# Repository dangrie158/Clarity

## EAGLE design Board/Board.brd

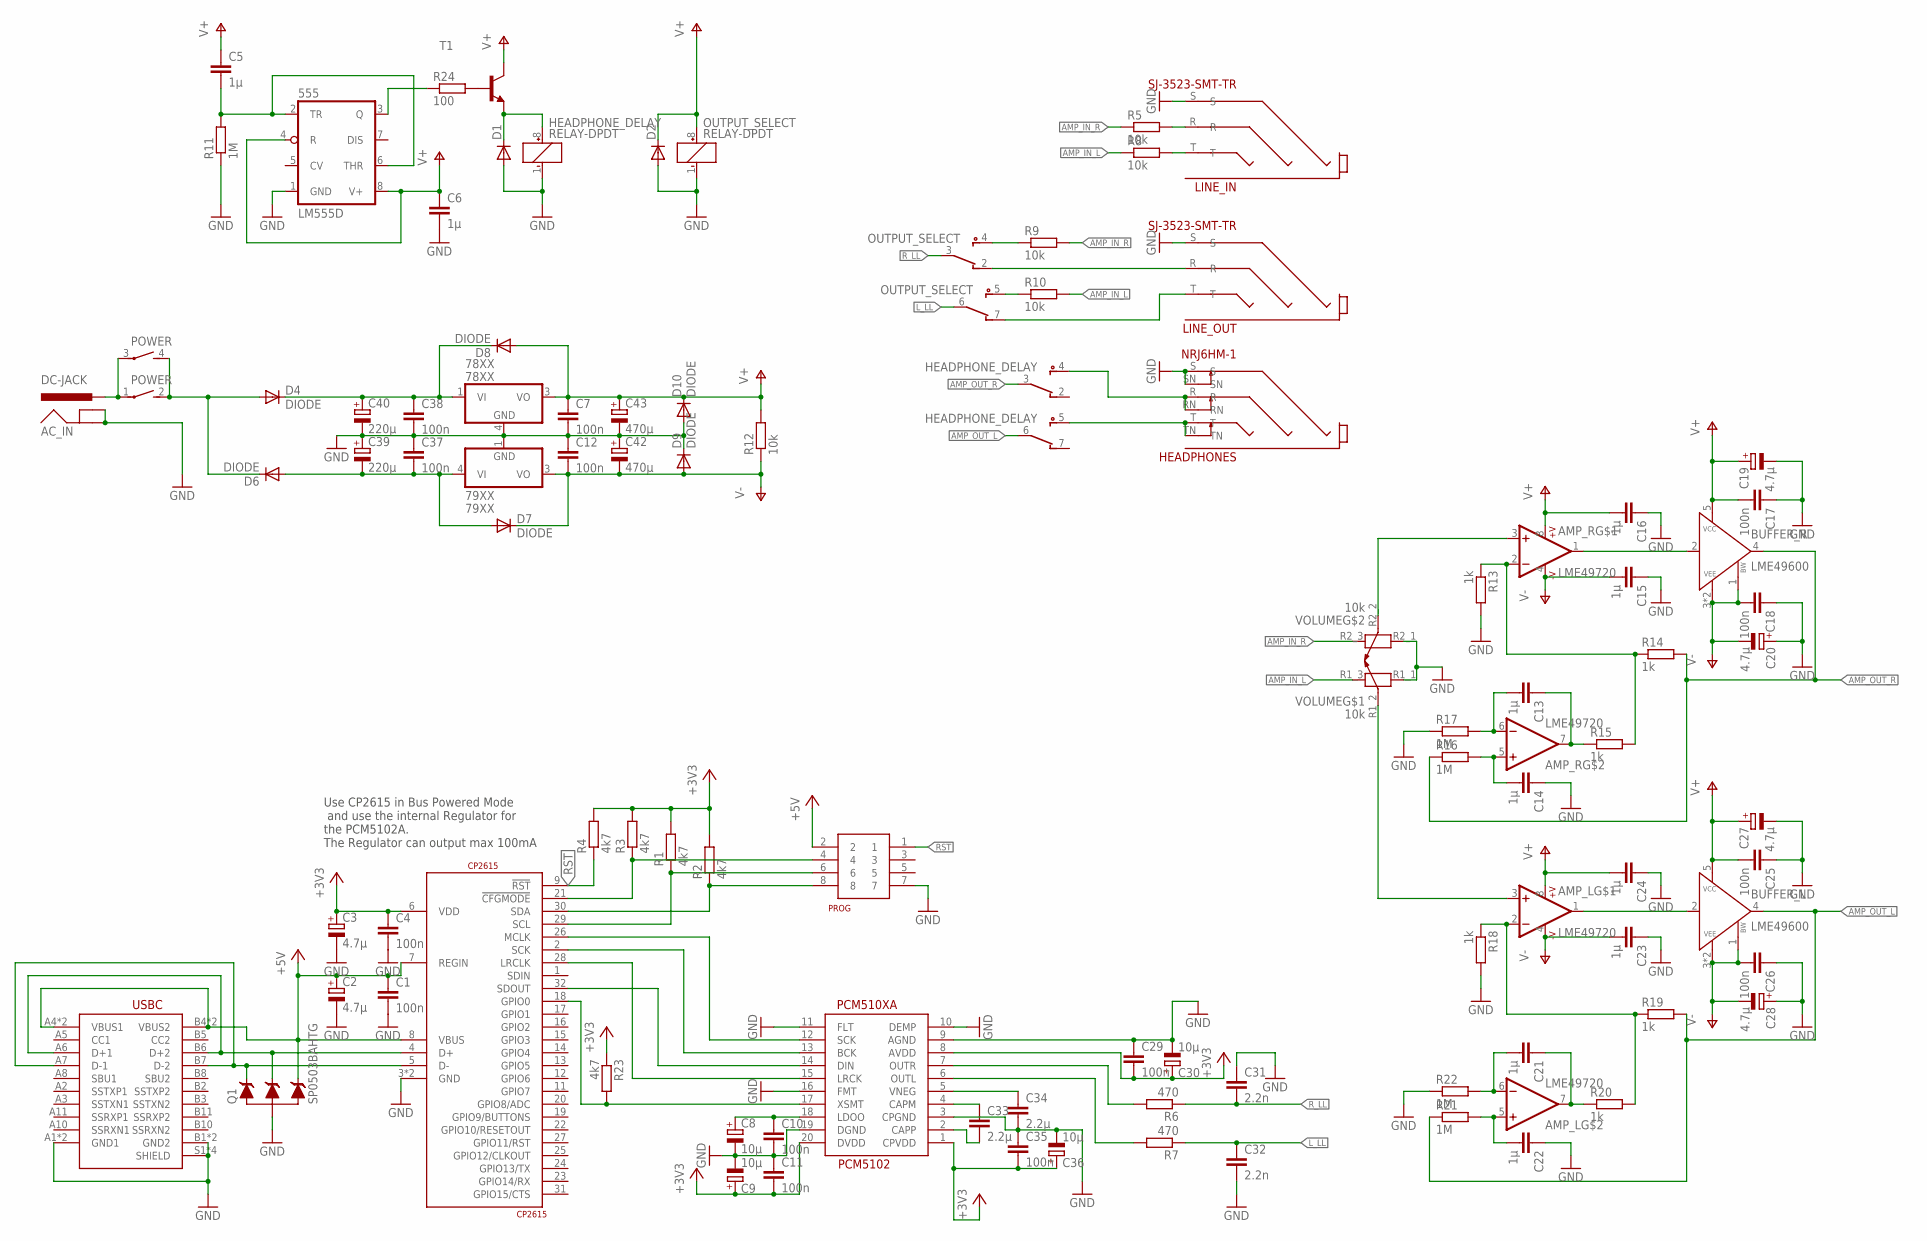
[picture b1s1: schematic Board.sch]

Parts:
78XX: 78XX; D2PAK
79XX: 79XX; D2PAK
555: LM555D; SO08
AC_IN: DC-JACK; POWER_JACK_PTH
AMP_L: LME49720; SOIC127P600X175-8
AMP_R: LME49720; SOIC127P600X175-8
BUFFER_L: LME49600; TO170P1238X470-6
BUFFER_R: LME49600; TO170P1238X470-6
C1, C4, C7, C10, C11, C12, C17, C18, C25, C26, C29, C35, C37, C38: 100n; C0603
C2, C3: 4.7µ; UD-4X5,8_NICHICON
C5, C6, C13, C14, C15, C16, C21, C22, C23, C24: 1µ; C0603
C8, C9, C30, C36: 10µ; UD-4X5,8_NICHICON
C19, C20, C27, C28: 4.7µ; SMC_A
C31, C32: 2.2n; C0603
C33, C34: 2.2µ; C0603
C39, C40: 220µ; 175TMP-0810
C42, C43: 470µ; 175TMP-0810
CP2615: CP2615; QFN50P500X500X90-32
D1, D2: DIODE-SOD323-W; SOD323-W
D4, D6, D7, D8, D9, D10: DIODE; SODFL5024X231
HEADPHONES: NRJ6HM-1
HEADPHONE_DELAY: RELAY-DPDT; KEMET-UD2
LINE_IN: SJ-3523-SMT-TR; SJ-352X-SMT-TR
LINE_OUT: SJ-3523-SMT-TR; SJ-352X-SMT-TR
OUTPUT_SELECT: RELAY-DPDT; KEMET-UD2
PCM5102: PCM510XA; SOP65P640X120-20
POWER: PB400
PROG: 2X4_HEADER; 2X4_0.5_HEADER_SMD
Q1: SP0503BAHTG; SOT192P237X122-4
R1, R2, R3, R4, R23: 4k7; R0603
R5, R8, R9, R10, R12: 10k; R0603
R6, R7: 470; R0603
R11, R16, R17, R21, R22: 1M; R0603
R13, R14, R15, R18, R19, R20: 1k; R0603
R24: 100; R0603
T1: BC817-16-NPN-SOT23-BEC; SOT23-BEC
U$2: UJ31-CH-3-SMT-TR
VOLUME: 10k; ALPS-RK09L12B0

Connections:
+3V3: C3.+, C4.1, C9.+, C11.2, C29.2, C30.+, C35.2, C36.+, CP2615.6 (VDD), PCM5102.1 (CPVDD), PCM5102.8 (AVDD), PCM5102.20 (DVDD), R1.2, R2.2, R3.2, R4.2, R23.1
+5V: C1.1, C2.+, CP2615.7 (REGIN), CP2615.8 (VBUS), PROG.2, Q1.4 (C3), U$2.A4 (VBUS1), U$2.A9 (VBUS1), U$2.B4 (VBUS2), U$2.B9 (VBUS2)
AMP_IN_L: R8.1, R10.2, VOLUME.R1_3 (2)
AMP_IN_R: R5.1, R9.2, VOLUME.R2_3 (2)
AMP_OUT_L: BUFFER_L.4 (OUT), HEADPHONE_DELAY.6 (W), R19.2, R21.1
AMP_OUT_R: BUFFER_R.4 (OUT), HEADPHONE_DELAY.3 (W), R14.2, R16.1
GND: 78XX.4 (GND), 79XX.1 (GND), 555.1 (GND), AC_IN.GND, AC_IN.GNDBREAK, C1.2, C2.-, C3.-, C4.2, C6.2, C7.2, C8.-, C9.-, C10.2, C11.1, C12.1, C14.1, C15.1, C16.1, C17.1, C18.1, C19.-, C20.+, C22.1, C23.1, C24.1, C25.1, C26.1, C27.-, C28.+, C29.1, C30.-, C31.1, C32.2, C34.2, C35.1, C36.-, C37.1, C38.2, C39.+, C40.-, C42.+, C43.-, CP2615.3 (GND), CP2615.PAD (GND), D1.A, D2.A, D9.C, D10.A, HEADPHONES.S, HEADPHONES.SN, HEADPHONE_DELAY.1 (-), LINE_IN.S, LINE_OUT.S, OUTPUT_SELECT.1 (-), PCM5102.3 (CPGND), PCM5102.9 (AGND), PCM5102.10 (DEMP), PCM5102.11 (FLT), PCM5102.16 (FMT), PCM5102.19 (DGND), PROG.7, Q1.1 (A), R11.1, R13.2, R17.1, R18.2, R22.1, U$2.A1 (GND1), U$2.A12 (GND1), U$2.B1 (GND2), U$2.B12 (GND2), U$2.S1 (SHIELD), U$2.S2 (SHIELD), U$2.S3 (SHIELD), U$2.S4 (SHIELD), VOLUME.R1_1 (1), VOLUME.R2_1 (1)
L_LL: C32.1, OUTPUT_SELECT.6 (W), R7.1
unnamed: CP2615.26 (MCLK), PCM5102.12 (SCK)
unnamed: AMP_L.3 (+IN), VOLUME.R1_2 (3)
unnamed: C33.1, PCM5102.4 (CAPM)
unnamed: C33.2, PCM5102.2 (CAPP)
unnamed: CP2615.32 (SDOUT), PCM5102.14 (DIN)
unnamed: CP2615.28 (LRCLK), PCM5102.15 (LRCK)
unnamed: CP2615.2 (SCK), PCM5102.13 (BCK)
unnamed: CP2615.21 (!CFGMODE), PROG.4, R3.1
unnamed: C8.+, C10.1, PCM5102.18 (LDOO)
unnamed: CP2615.5 (D-), Q1.2 (C1), U$2.A7 (D-1), U$2.B7 (D-2)
unnamed: CP2615.4 (D+), Q1.3 (C2), U$2.A6 (D+1), U$2.B6 (D+2)
unnamed: C34.1, PCM5102.5 (VNEG)
unnamed: CP2615.30 (SDA), PROG.8, R2.1
unnamed: LINE_OUT.R, OUTPUT_SELECT.2 (NC)
unnamed: CP2615.29 (SCL), PROG.6, R1.1
unnamed: AMP_L.2 (-IN), R18.1, R19.1, R20.2
unnamed: AMP_R.3 (+IN), VOLUME.R2_2 (3)
unnamed: AMP_R.2 (-IN), R13.1, R14.1, R15.2
unnamed: AMP_R.1 (OUT), BUFFER_R.2 (IN)
unnamed: LINE_OUT.T, OUTPUT_SELECT.7 (NC)
unnamed: AMP_R.7 (OUT), C13.1, R15.1
unnamed: AMP_R.5 (+IN), C14.2, R16.2
unnamed: HEADPHONES.T, HEADPHONES.TN, HEADPHONE_DELAY.5 (NO)
unnamed: AMP_R.6 (-IN), C13.2, R17.2
unnamed: AMP_L.1 (OUT), BUFFER_L.2 (IN)
unnamed: AMP_L.7 (OUT), C21.1, R20.1
unnamed: AMP_L.5 (+IN), C22.2, R21.2
unnamed: HEADPHONES.R, HEADPHONES.RN, HEADPHONE_DELAY.4 (NO)
unnamed: AMP_L.6 (-IN), C21.2, R22.2
unnamed: AC_IN.PWR, POWER.1, POWER.3
unnamed: CP2615.18 (GPIO0), PCM5102.17 (XSMT), R23.2
unnamed: LINE_IN.R, R5.2
unnamed: PCM5102.7 (OUTR), R6.2
unnamed: PCM5102.6 (OUTL), R7.2
unnamed: LINE_IN.T, R8.2
unnamed: OUTPUT_SELECT.5 (NO), R10.1
unnamed: OUTPUT_SELECT.4 (NO), R9.1
unnamed: D4.A, D6.C, POWER.2 (S), POWER.4 (S)
unnamed: 555.2 (TR), 555.6 (THR), C5.2, R11.2
unnamed: 79XX.4 (VI), C37.2, C39.-, D6.A, D7.A
unnamed: 78XX.1 (VI), C38.1, C40.+, D4.C, D8.C
unnamed: 555.3 (Q), R24.1
unnamed: R24.2, T1.B
unnamed: D1.C, HEADPHONE_DELAY.8 (+), T1.E
RST: CP2615.9 (!RST), PROG.1, R4.1
R_LL: C31.2, OUTPUT_SELECT.3 (W), R6.1
V+: 78XX.3 (VO), 555.4 (R), 555.8 (V+), AMP_L.8 (+V), AMP_R.8 (+V), BUFFER_L.5 (VCC), BUFFER_R.5 (VCC), C5.1, C6.1, C7.1, C16.2, C17.2, C19.+, C24.2, C25.2, C27.+, C43.+, D2.C, D8.A, D10.C, OUTPUT_SELECT.8 (+), R12.2, T1.C
V-: 79XX.3 (VO), AMP_L.4 (GND), AMP_R.4 (GND), BUFFER_L.1 (BW), BUFFER_L.3 (VEE), BUFFER_L.6 (VEE), BUFFER_R.1 (BW), BUFFER_R.3 (VEE), BUFFER_R.6 (VEE), C12.2, C15.2, C18.2, C20.-, C23.2, C26.2, C28.-, C42.-, D7.C, D9.A, R12.1

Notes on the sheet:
Use CP2615 in Bus Powered Mode and use the internal Regulator for the PCM5102A. The Regulator can output max 100mA

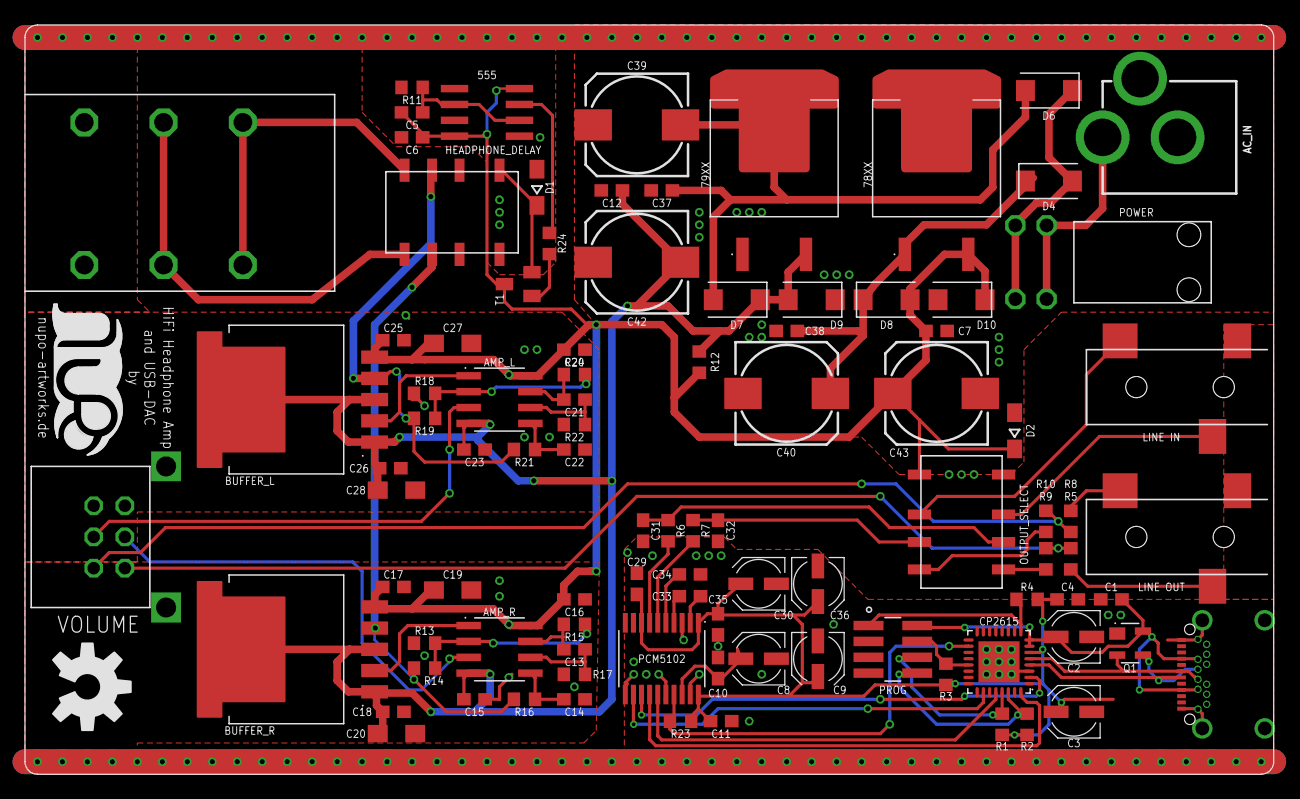
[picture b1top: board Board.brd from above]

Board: 2 copper layers, 100.0 x 60.0 mm, 97 parts (0 on the bottom side), 56 nets.

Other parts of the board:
U$1: LOGO-SILKSCREEN
U$3: OSHW-LOGO-L

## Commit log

2018-03-31 added OSHW Logo
2018-03-31 added gitignore
2018-03-31 fixed relay orientation to face powersupply
2018-03-31 fixed overlayp
2018-03-31 fixed silkscreen issue
2018-03-31 fixed bad via location
2018-04-06 updated relay orientation

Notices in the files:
parts and their libraries:
SparkFun-Aesthetics: Licensing: Creative Commons ShareAlike 4.0 International - https://creativecommons.org/licenses/by-sa/4.0
